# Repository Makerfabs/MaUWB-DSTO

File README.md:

# Makerfabs MaUWB DSTO

## Introduce

[Product Link]()

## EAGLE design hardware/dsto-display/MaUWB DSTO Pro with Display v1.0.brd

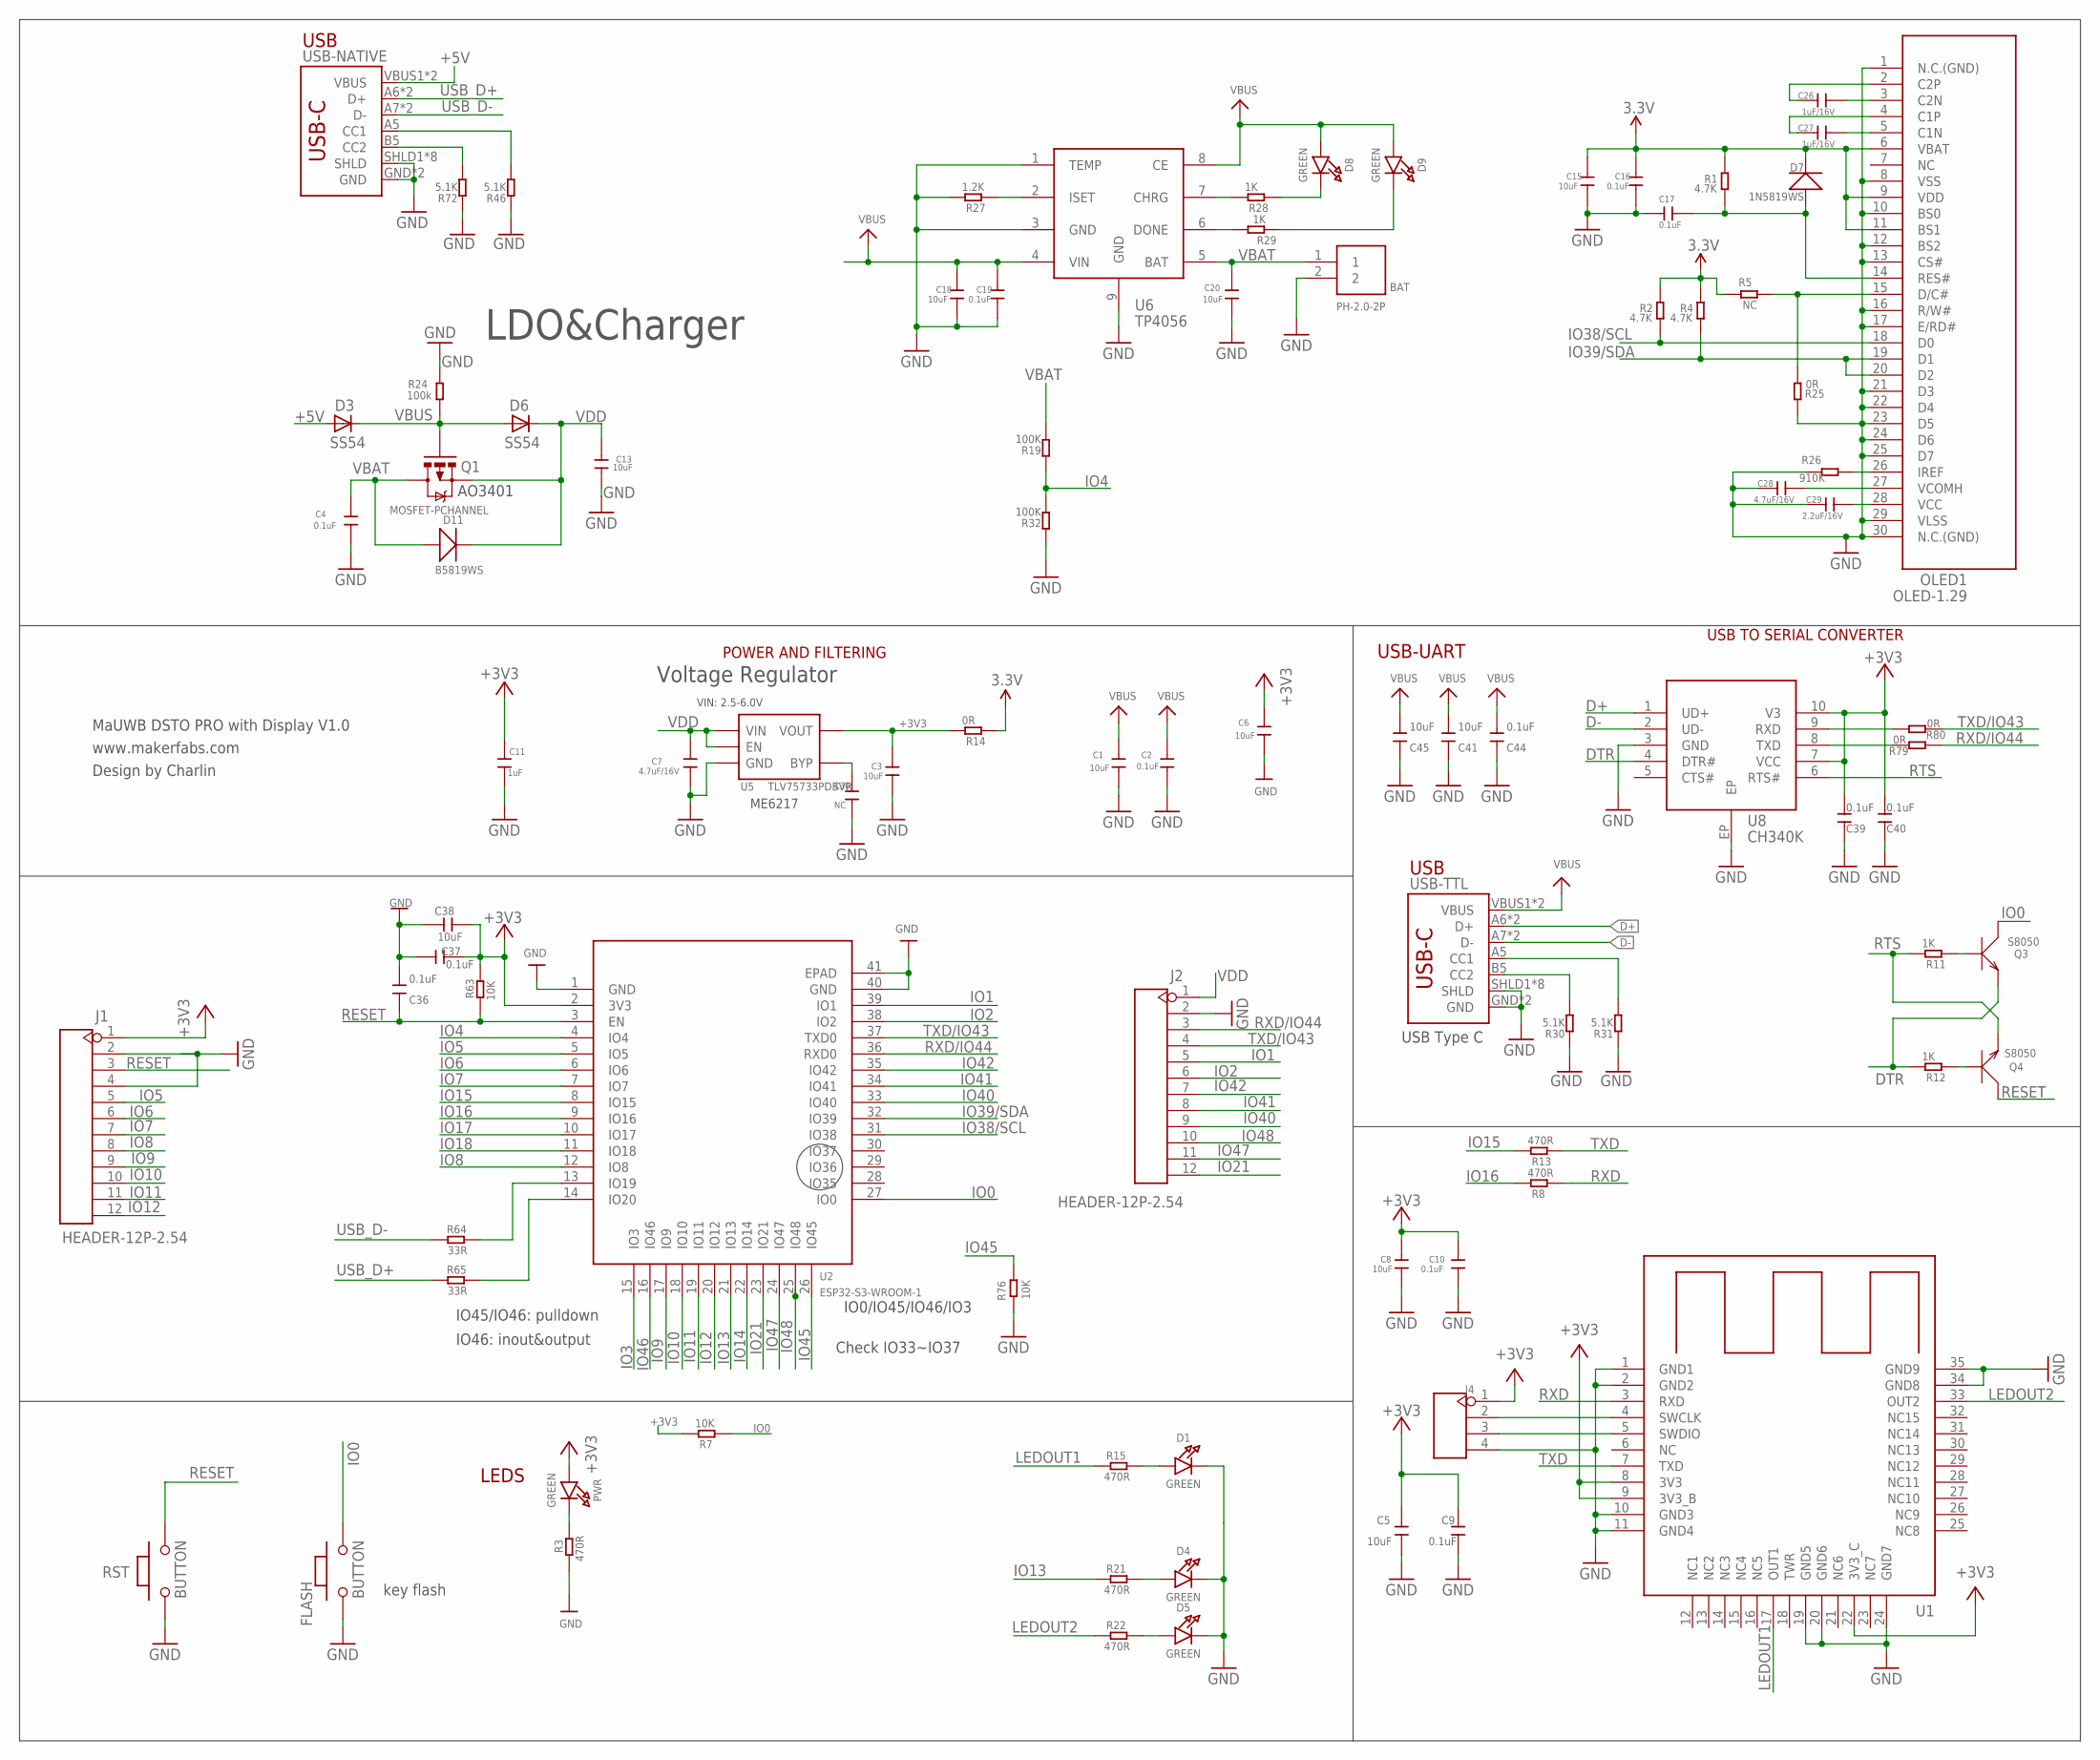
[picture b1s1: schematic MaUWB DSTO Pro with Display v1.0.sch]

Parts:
BAT: PH-2.0-2P
C1, C3, C6, C8, C13, C15, C18, C20: 10uF; 0603
C2, C4, C10, C16, C17, C19: 0.1uF; 0603
C5: 10uF; DISCRETE_C0402
C7, C28: 4.7uF/16V; 0603
C9: 0.1uF; DISCRETE_C0402
C11: 1uF; 0603
C26, C27: 1uF/16V; 0603
C29: 2.2uF/16V; 0603
C30: NC; 0603
C36, C37, C39, C40, C44: 0.1uF; DISCRETE_C0603
C38, C41, C45: 10uF; DISCRETE_C0603
D1, D4, D5, D8, D9: GREEN; CHIPLED_0805_NOOUTLINE
D3, D6: SS54; DO-214AC
D7: 1N5819WS; SOD323
D11: B5819WS; SOD323
FLASH: BUTTON; 157SW
J1, J2: HEADER-12P-2.54; 12P-2.54
J4: HEADER-4P-60/35MILROUND; 4P-65/35ROUND
OLED1: OLED-1.29
PWR: GREEN; CHIPLED_0805_NOOUTLINE
Q1: MOSFET-PCHANNEL; SOT23-3
Q3, Q4: S8050; SOT23
R1, R2, R4: 4.7K; R0603
R3, R8, R13, R15, R21, R22: 470R; R0603
R5: NC; R0603
R7, R63, R76: 10K; R0603
R11, R12, R28, R29: 1K; R0603
R14, R25, R79, R80: 0R; R0603
R19, R32: 100K; DISCRETE_R0603
R24: 100k; R0603
R26: 910K; R0603
R27: 1.2K; R0603
R30, R31, R46, R72: 5.1K; DISCRETE_R0603
R64, R65: 33R; R0603
RST: BUTTON; 157SW
U1: UWB-DSTO
U2: ESP32-S3-WROOM-1
U5: TLV75733PDBVR; SOT23-5
U6: TP4056; SOP8-1.27P
U8: CH340K; ESOP-10-EP-150MIL
USB-NATIVE: USB_C5; USB-C-16P-5
USB-TTL: USB_C5; USB-C-16P-5

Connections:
3.3V: C15.1, C16.1, D7.-, OLED1.6 (VBAT), OLED1.9 (VDD), OLED1.11 (BS1), R1.2, R2.2, R4.2, R5.2, R14.1
+3V3: C3.1, C5.2, C6.1, C8.1, C9.2, C10.1, C11.1, C37.1, C38.1, C39.2, C40.2, J1.1, J4.1, PWR.A, R7.2, R14.2, R63.2, U1.8 (3V3), U1.9 (3V3_B), U1.22 (3V3_C), U2.2 (3V3), U5.5 (VOUT), U8.7 (VCC), U8.10 (V3)
+5V: D3.A, USB-NATIVE.VBUS1 (VBUS), USB-NATIVE.VBUS2 (VBUS)
D+: U8.1 (UD+), USB-TTL.A6 (D+), USB-TTL.B6 (D+)
D-: U8.2 (UD-), USB-TTL.A7 (D-), USB-TTL.B7 (D-)
DTR: Q3.2 (E), R12.2, U8.4 (DTR#)
GND: BAT.2, C1.2, C2.2, C3.2, C4.2, C5.1, C6.2, C7.2, C8.2, C9.1, C10.2, C11.2, C13.1, C15.2, C16.2, C17.1, C18.2, C19.2, C20.2, C28.1, C29.1, C30.2, C36.2, C37.2, C38.2, C39.1, C40.1, C41.1, C44.1, C45.1, D1.C, D4.C, D5.C, FLASH.1, J1.2, J1.4, J2.2, J4.4, OLED1.1 (N.C.(GND)), OLED1.8 (VSS), OLED1.10 (BS0), OLED1.12 (BS2), OLED1.13 (CS#), OLED1.16 (R/W#), OLED1.17 (E/RD#), OLED1.21 (D3), OLED1.22 (D4), OLED1.23 (D5), OLED1.24 (D6), OLED1.25 (D7), OLED1.29 (VLSS), OLED1.30 (N.C.(GND)), R3.1, R24.2, R25.2, R26.2, R27.2, R30.1, R31.1, R32.1, R46.1, R72.1, R76.1, RST.1, U1.1 (GND1), U1.2 (GND2), U1.10 (GND3), U1.11 (GND4), U1.19 (GND5), U1.20 (GND6), U1.24 (GND7), U1.34 (GND8), U1.35 (GND9), U2.1 (GND), U2.40 (GND), U2.41 (EPAD), U5.2 (GND), U6.1 (TEMP), U6.3 (GND), U6.9 (GND), U8.3 (GND), U8.EP, USB-NATIVE.GND, USB-NATIVE.GND2 (GND), USB-NATIVE.SHLD1 (SHLD), USB-NATIVE.SHLD2 (SHLD), USB-NATIVE.SHLD3 (SHLD), USB-NATIVE.SHLD4 (SHLD), USB-NATIVE.SHLD5 (SHLD), USB-NATIVE.SHLD6 (SHLD), USB-NATIVE.SHLD7 (SHLD), USB-NATIVE.SHLD8 (SHLD), USB-TTL.GND, USB-TTL.GND2 (GND), USB-TTL.SHLD1 (SHLD), USB-TTL.SHLD2 (SHLD), USB-TTL.SHLD3 (SHLD), USB-TTL.SHLD4 (SHLD), USB-TTL.SHLD5 (SHLD), USB-TTL.SHLD6 (SHLD), USB-TTL.SHLD7 (SHLD), USB-TTL.SHLD8 (SHLD)
IO0: FLASH.2, Q3.3 (C), R7.1, U2.27 (IO0)
IO1: J2.5, U2.39 (IO1)
IO2: J2.6, U2.38 (IO2)
IO3: U2.15 (IO3)
IO4: R19.1, R32.2, U2.4 (IO4)
IO5: J1.5, U2.5 (IO5)
IO6: J1.6, U2.6 (IO6)
IO7: J1.7, U2.7 (IO7)
IO8: J1.8, U2.12 (IO8)
IO9: J1.9, U2.17 (IO9)
IO10: J1.10, U2.18 (IO10)
IO11: J1.11, U2.19 (IO11)
IO12: J1.12, U2.20 (IO12)
IO13: R21.1, U2.21 (IO13)
IO14: U2.22 (IO14)
IO15: R13.2, U2.8 (IO15)
IO16: R8.2, U2.9 (IO16)
IO17: U2.10 (IO17)
IO18: U2.11 (IO18)
IO21: J2.12, U2.23 (IO21)
IO38/SCL: OLED1.18 (D0), R2.1, U2.31 (IO38)
IO39/SDA: OLED1.19 (D1), OLED1.20 (D2), R4.1, U2.32 (IO39)
IO40: J2.9, U2.33 (IO40)
IO41: J2.8, U2.34 (IO41)
IO42: J2.7, U2.35 (IO42)
IO45: R76.2, U2.26 (IO45)
IO46: U2.16 (IO46)
IO47: J2.11, U2.24 (IO47)
IO48: J2.10, U2.25 (IO48)
LEDOUT1: R15.1, U1.17 (OUT1)
LEDOUT2: R22.1, U1.33 (OUT2)
unnamed: D1.A, R15.2
unnamed: R64.2, U2.13 (IO19)
unnamed: C17.2, D7.+, OLED1.14 (RES#), R1.1
unnamed: OLED1.15 (D/C#), R5.1, R25.1
unnamed: PWR.C, R3.2
unnamed: C28.2, OLED1.27 (VCOMH)
unnamed: C26.2, OLED1.3 (C2N)
unnamed: C29.2, OLED1.28 (VCC)
unnamed: OLED1.26 (IREF), R26.1
unnamed: J4.3, U1.5 (SWDIO)
unnamed: Q4.1 (B), R12.1
unnamed: Q3.1 (B), R11.1
unnamed: J4.2, U1.4 (SWCLK)
unnamed: D4.A, R21.2
unnamed: D5.A, R22.2
unnamed: C26.1, OLED1.2 (C2P)
unnamed: C27.1, OLED1.4 (C1P)
unnamed: C27.2, OLED1.5 (C1N)
unnamed: R27.1, U6.2 (ISET)
unnamed: R31.2, USB-TTL.A5 (CC1)
unnamed: R30.2, USB-TTL.B5 (CC2)
unnamed: R28.2, U6.7 (CHRG)
unnamed: R29.2, U6.6 (DONE)
unnamed: D8.C, R28.1
unnamed: D9.C, R29.1
unnamed: R46.2, USB-NATIVE.A5 (CC1)
unnamed: R72.2, USB-NATIVE.B5 (CC2)
unnamed: R65.2, U2.14 (IO20)
unnamed: R80.2, U8.9 (RXD)
unnamed: R79.2, U8.8 (TXD)
unnamed: C30.1, U5.4 (BYP)
RESET: C36.1, J1.3, Q4.3 (C), R63.1, RST.2, U2.3 (EN)
RTS: Q4.2 (E), R11.2, U8.6 (RTS#)
RXD: R8.1, U1.3 (RXD)
RXD/IO44: J2.3, R79.1, U2.36 (RXD0)
TXD: R13.1, U1.7 (TXD)
TXD/IO43: J2.4, R80.1, U2.37 (TXD0)
USB_D+: R65.1, USB-NATIVE.A6 (D+), USB-NATIVE.B6 (D+)
USB_D-: R64.1, USB-NATIVE.A7 (D-), USB-NATIVE.B7 (D-)
VBAT: BAT.1, C4.1, C20.1, D11.+, Q1.3 (D), R19.2, U6.5 (BAT)
VBUS: C1.1, C2.1, C18.1, C19.1, C41.2, C44.2, C45.2, D3.C, D6.A, D8.A, D9.A, Q1.1 (G), R24.1, U6.4 (VIN), U6.8 (CE), USB-TTL.VBUS1 (VBUS), USB-TTL.VBUS2 (VBUS)
VDD: C7.1, C13.2, D6.C, D11.-, J2.1, Q1.2 (S), U5.1 (VIN), U5.3 (EN)

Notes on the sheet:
USB-UART
LEDS
POWER AND FILTERING
key flash
MaUWB DSTO PRO with Display V1.0
Voltage Regulator
VIN: 2.5-6.0V
USB
USB Type C
LDO&Charger
AO3401
ME6217
USB TO SERIAL CONVERTER
IO45/IO46: pulldown
IO46: inout&output
IO0/IO45/IO46/IO3
Check IO33~IO37
www.makerfabs.com
Design by Charlin

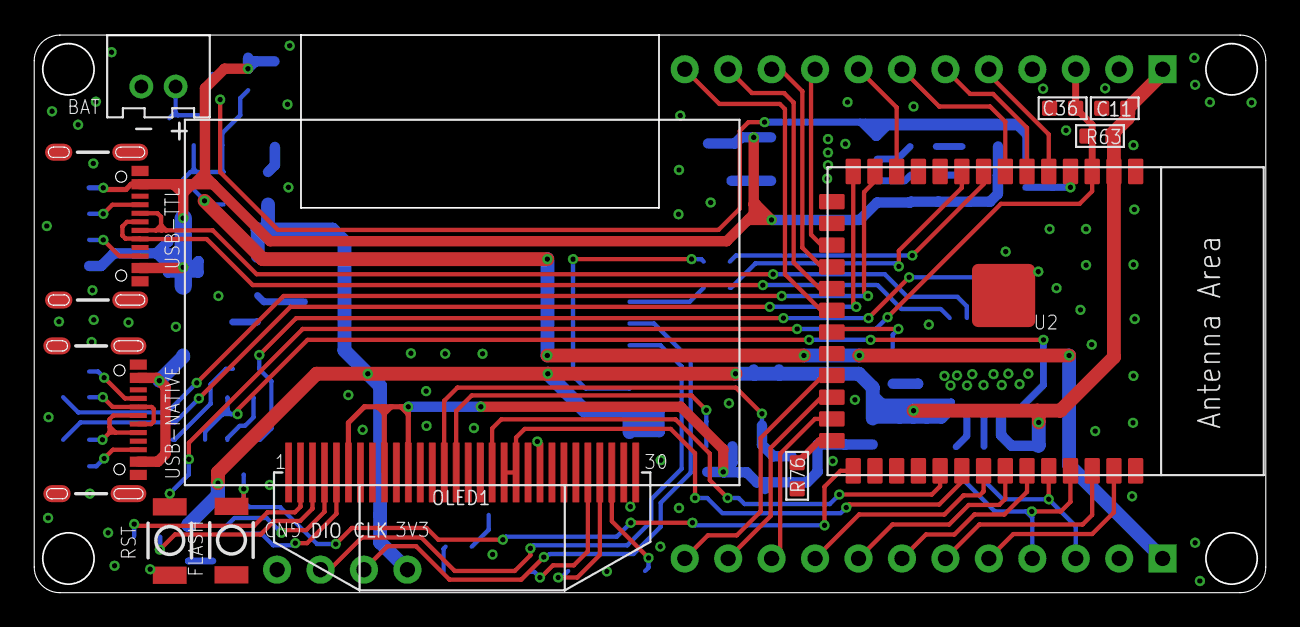
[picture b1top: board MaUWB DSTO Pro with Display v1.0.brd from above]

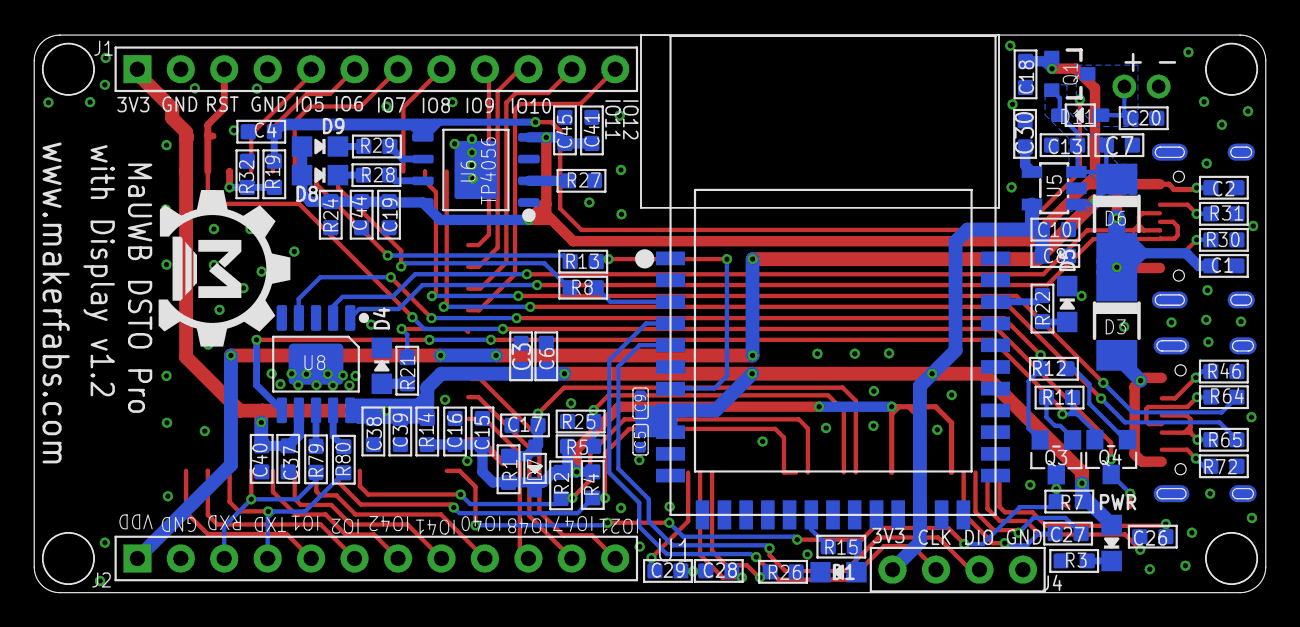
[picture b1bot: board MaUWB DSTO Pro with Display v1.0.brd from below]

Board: 2 copper layers, 72.0 x 32.6 mm, 91 parts (80 on the bottom side), 75 nets.

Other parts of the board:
U$1: MAKERFABS_0.3

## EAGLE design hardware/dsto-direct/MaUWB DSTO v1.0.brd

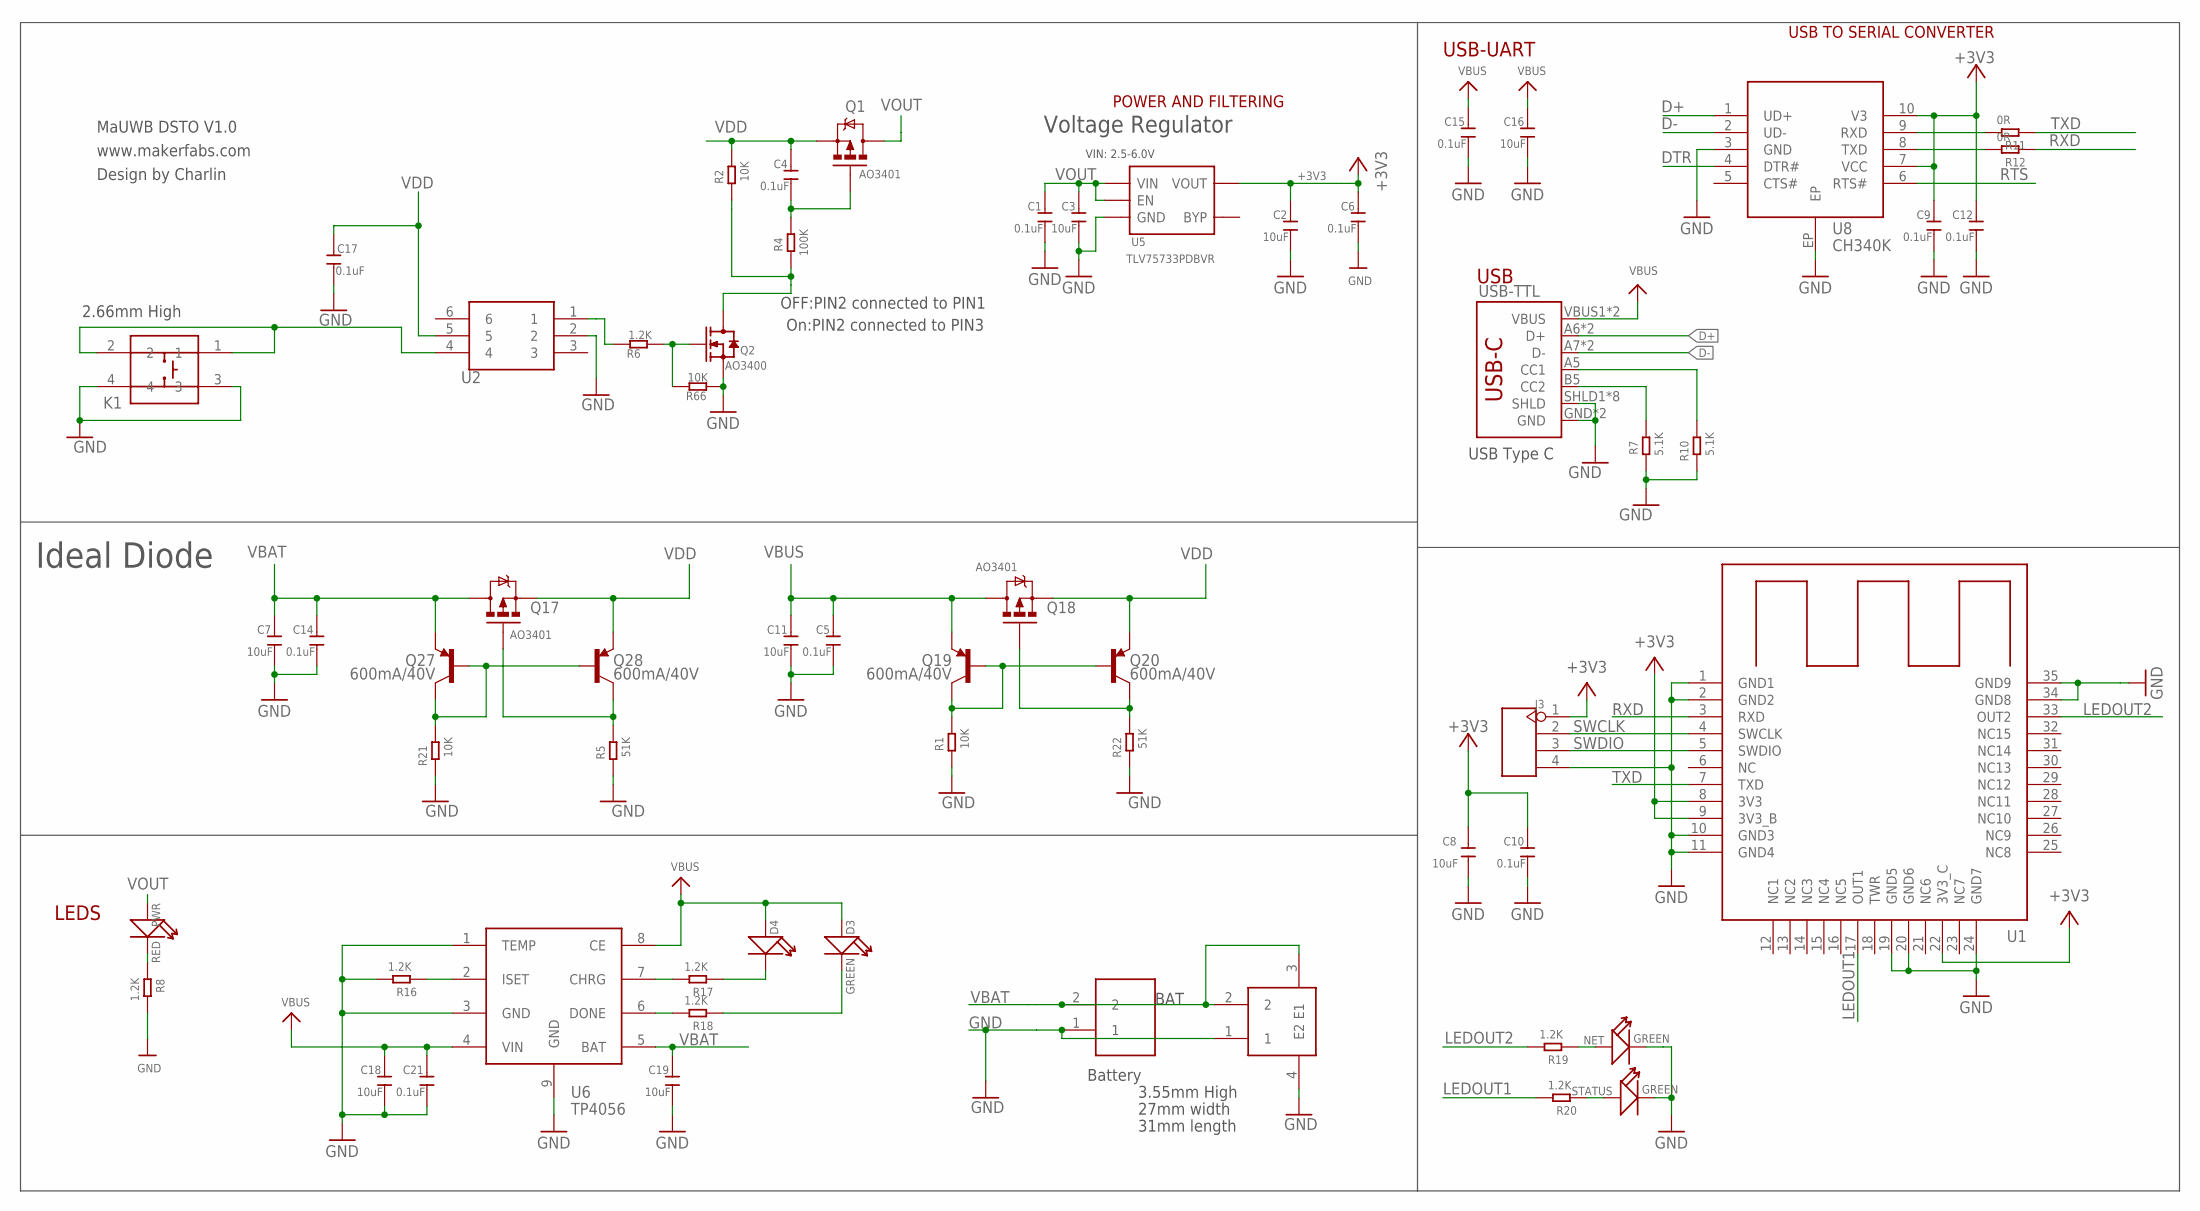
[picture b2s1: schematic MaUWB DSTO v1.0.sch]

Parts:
BAT: PH2.0-2P-90-DIP
C1, C4, C5, C6, C9, C10, C12, C14, C15, C17, C21: 0.1uF; DISCRETE_C0402
C2, C3, C7, C8, C11, C16, C18, C19: 10uF; DISCRETE_C0402
D3: GREEN; DISCRETE_LED-0603
D4: DISCRETE_LED0603; DISCRETE_LED-0603
J2: JST-ACH1.2-2P; A1203WRS-2P
J3: HEADER-4P-60/35MILROUND; 4P-65/35ROUND
K1: BTN01A
NET: GREEN; DISCRETE_LED-0603
PWR: RED; DISCRETE_LED-0603
Q1, Q17, Q18: AO3401; SOT23-3
Q2: AO3400; SOT23@1
Q19, Q20, Q27, Q28: 600mA/40V; SOT23-3
R1, R2, R21, R66: 10K; DISCRETE_R0402
R4: 100K; DISCRETE_R0402
R5, R22: 51K; DISCRETE_R0402
R6, R8, R16, R17, R18, R19, R20: 1.2K; DISCRETE_R0402
R7, R10: 5.1K; DISCRETE_R0402
R11, R12: 0R; DISCRETE_R0402
STATUS: GREEN; DISCRETE_LED-0603
U1: UWB-DSTO
U2: SW01A; SOT23-6-95P-300L300W
U5: TLV75733PDBVR; SOT23-5
U6: TP4056; SOP8-1.27P
U8: CH340K; ESOP-10-EP-150MIL
USB-TTL: USB_C5; USB-C-16P-5

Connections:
+3V3: C2.2, C6.2, C8.2, C9.2, C10.2, C12.2, J3.1, U1.8 (3V3), U1.9 (3V3_B), U1.22 (3V3_C), U5.5 (VOUT), U8.7 (VCC), U8.10 (V3)
D+: U8.1 (UD+), USB-TTL.A6 (D+), USB-TTL.B6 (D+)
D-: U8.2 (UD-), USB-TTL.A7 (D-), USB-TTL.B7 (D-)
DTR: U8.4 (DTR#)
GND: BAT.1, C1.1, C2.1, C3.1, C5.1, C6.1, C7.1, C8.1, C9.1, C10.1, C11.1, C12.1, C14.1, C15.1, C16.1, C17.1, C18.1, C19.1, C21.1, J2.1, J2.4 (E2), J3.4, K1.3, K1.4, NET.-, Q2.2 (S), R1.1, R5.1, R7.1, R8.2, R10.1, R16.2, R21.1, R22.1, R66.1, STATUS.-, U1.1 (GND1), U1.2 (GND2), U1.10 (GND3), U1.11 (GND4), U1.19 (GND5), U1.20 (GND6), U1.24 (GND7), U1.34 (GND8), U1.35 (GND9), U2.2, U5.2 (GND), U6.1 (TEMP), U6.3 (GND), U6.9 (GND), U8.3 (GND), U8.EP, USB-TTL.GND, USB-TTL.GND2 (GND), USB-TTL.SHLD1 (SHLD), USB-TTL.SHLD2 (SHLD), USB-TTL.SHLD3 (SHLD), USB-TTL.SHLD4 (SHLD), USB-TTL.SHLD5 (SHLD), USB-TTL.SHLD6 (SHLD), USB-TTL.SHLD7 (SHLD), USB-TTL.SHLD8 (SHLD)
LEDOUT1: R20.2, U1.17 (OUT1)
LEDOUT2: R19.2, U1.33 (OUT2)
unnamed: NET.+, R19.1
unnamed: Q19.1 (B), Q19.3 (C), Q20.1 (B), R1.2
unnamed: Q18.1 (G), Q20.3 (C), R22.2
unnamed: C4.1, Q1.1 (G), R4.2
unnamed: PWR.-, R8.1
unnamed: Q2.3 (D), R2.1, R4.1
unnamed: K1.1, K1.2, U2.4
unnamed: R6.2, U2.1
unnamed: R7.2, USB-TTL.B5 (CC2)
unnamed: R10.2, USB-TTL.A5 (CC1)
unnamed: R20.1, STATUS.+
unnamed: Q2.1 (G), R6.1, R66.2
unnamed: R16.1, U6.2 (ISET)
unnamed: R17.2, U6.7 (CHRG)
unnamed: R18.2, U6.6 (DONE)
unnamed: D4.-, R17.1
unnamed: D3.-, R18.1
unnamed: R11.2, U8.9 (RXD)
unnamed: R12.2, U8.8 (TXD)
unnamed: Q17.1 (G), Q28.3 (C), R5.2
unnamed: Q27.1 (B), Q27.3 (C), Q28.1 (B), R21.2
RTS: U8.6 (RTS#)
RXD: R12.1, U1.3 (RXD)
SWCLK: J3.2, U1.4 (SWCLK)
SWDIO: J3.3, U1.5 (SWDIO)
TXD: R11.1, U1.7 (TXD)
VBAT: BAT.2, C7.2, C14.2, C19.2, J2.2, J2.3 (E1), Q17.3 (D), Q27.2 (E), U6.5 (BAT)
VBUS: C5.2, C11.2, C15.2, C16.2, C18.2, C21.2, D3.+, D4.+, Q18.3 (D), Q19.2 (E), U6.4 (VIN), U6.8 (CE), USB-TTL.VBUS1 (VBUS), USB-TTL.VBUS2 (VBUS)
VDD: C4.2, C17.2, Q1.2 (S), Q17.2 (S), Q18.2 (S), Q20.2 (E), Q28.2 (E), R2.2, U2.5
VOUT: C1.2, C3.2, PWR.+, Q1.3 (D), U5.1 (VIN), U5.3 (EN)

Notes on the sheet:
USB-UART
LEDS
POWER AND FILTERING
MaUWB DSTO V1.0
Voltage Regulator
VIN: 2.5-6.0V
USB
USB Type C
USB TO SERIAL CONVERTER
www.makerfabs.com
Design by Charlin
Ideal Diode
On:PIN2 connected to PIN3
OFF:PIN2 connected to PIN1
2.66mm High
Battery
BAT
3.55mm High
27mm width
31mm length

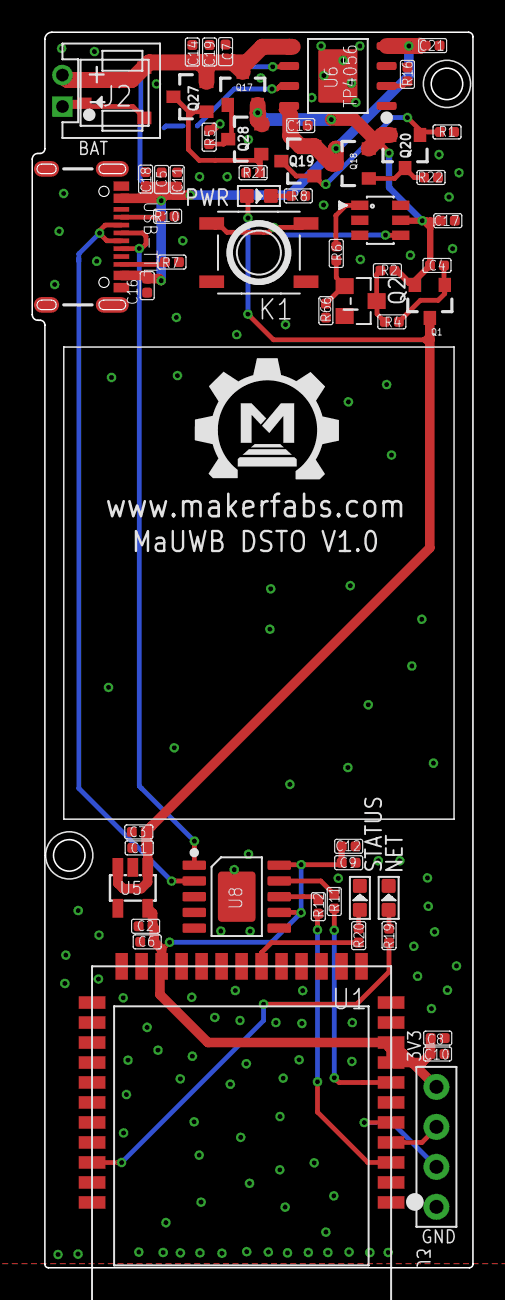
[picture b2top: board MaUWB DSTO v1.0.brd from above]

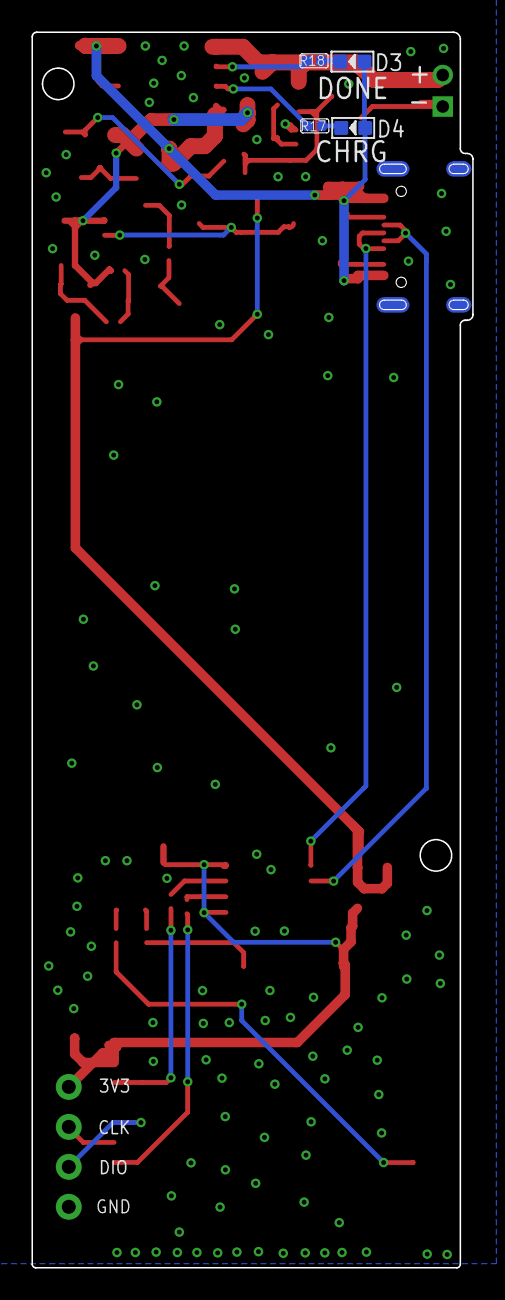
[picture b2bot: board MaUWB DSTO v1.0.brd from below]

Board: 2 copper layers, 28.0 x 78.5 mm, 61 parts (4 on the bottom side), 35 nets.

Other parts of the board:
U$1: MAKERFABS_0.3

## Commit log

2026-01-13 add hardware
2026-01-14 add docs verison
2026-01-16 update dsto-assistant

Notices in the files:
parts and their libraries:
User-Submitted: Licensing: Creative Commons ShareAlike 4.0 International - https://creativecommons.org/licenses/by-sa/4.0
microbuilder: This work is placed in the public domain, and may be freely used for commercial and non-commercial work with the following conditions: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
